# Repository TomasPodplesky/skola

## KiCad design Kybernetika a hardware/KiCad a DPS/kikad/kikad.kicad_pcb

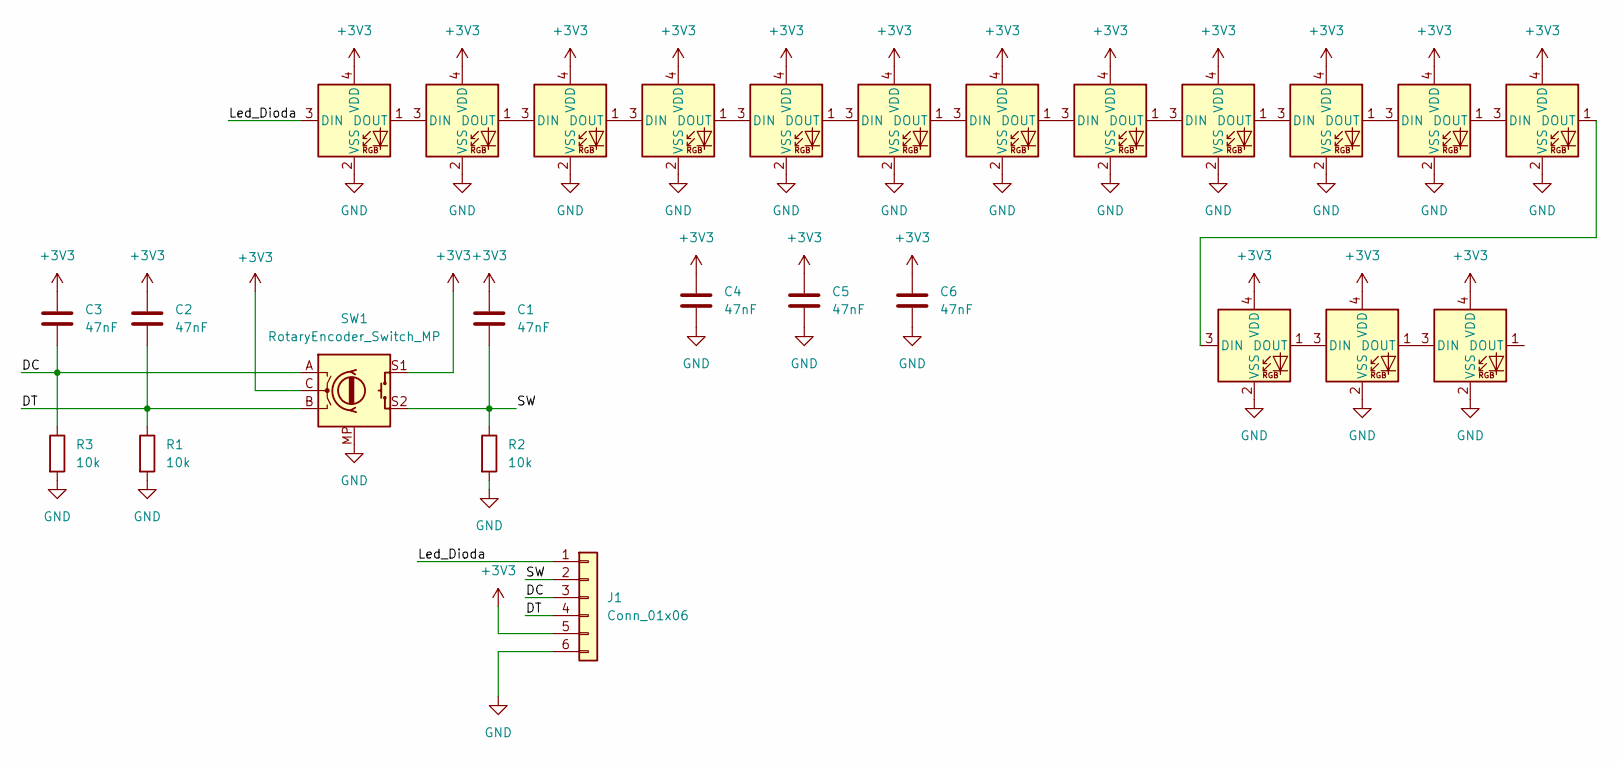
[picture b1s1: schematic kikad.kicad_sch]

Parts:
C1, C2, C3, C4, C5, C6: 47nF; C_0603_1608Metric_Pad1.08x0.95mm_HandSolder
D1, D2, D3, D4, D5, D6, D7, D8, D9, D10, D11, D12, D13, D14, D15: WS2812B-2020; LED_WS2812B-2020_PLCC4_2.0x2.0mm
J1: Conn_01x06; JST_XH_B6B-XH-AM_1x06_P2.50mm_Vertical
R1, R2, R3: 10k; R_0603_1608Metric_Pad0.98x0.95mm_HandSolder
SW1: RotaryEncoder_Switch_MP; RotaryEncoder_Alps_EC11E-Switch_Vertical_H20mm_CircularMoun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

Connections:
+3V3: C1.1, C2.1, C3.1, C4.1, C5.1, C6.1, D1.4 (VDD), D2.4 (VDD), D3.4 (VDD), D4.4 (VDD), D5.4 (VDD), D6.4 (VDD), D7.4 (VDD), D8.4 (VDD), D9.4 (VDD), D10.4 (VDD), D11.4 (VDD), D12.4 (VDD), D13.4 (VDD), D14.4 (VDD), D15.4 (VDD), J1.5, SW1.C, SW1.S1
/DC: C3.2, J1.3, R3.1, SW1.A
/DT: C2.2, J1.4, R1.1, SW1.B
/Led_Dioda: D1.3 (DIN), J1.1
/SW: C1.2, J1.2, R2.1, SW1.S2
GND: C4.2, C5.2, C6.2, D1.2 (VSS), D2.2 (VSS), D3.2 (VSS), D4.2 (VSS), D5.2 (VSS), D6.2 (VSS), D7.2 (VSS), D8.2 (VSS), D9.2 (VSS), D10.2 (VSS), D11.2 (VSS), D12.2 (VSS), D13.2 (VSS), D14.2 (VSS), D15.2 (VSS), J1.6, R1.2, R2.2, R3.2, SW1.MP
unnamed: D1.1 (DOUT), D2.3 (DIN)
unnamed: D2.1 (DOUT), D3.3 (DIN)
unnamed: D3.1 (DOUT), D4.3 (DIN)
unnamed: D4.1 (DOUT), D5.3 (DIN)
unnamed: D5.1 (DOUT), D6.3 (DIN)
unnamed: D6.1 (DOUT), D7.3 (DIN)
unnamed: D7.1 (DOUT), D8.3 (DIN)
unnamed: D8.1 (DOUT), D9.3 (DIN)
unnamed: D9.1 (DOUT), D10.3 (DIN)
unnamed: D10.1 (DOUT), D11.3 (DIN)
unnamed: D11.1 (DOUT), D12.3 (DIN)
unnamed: D12.1 (DOUT), D13.3 (DIN)
unnamed: D13.1 (DOUT), D14.3 (DIN)
unnamed: D14.1 (DOUT), D15.3 (DIN)

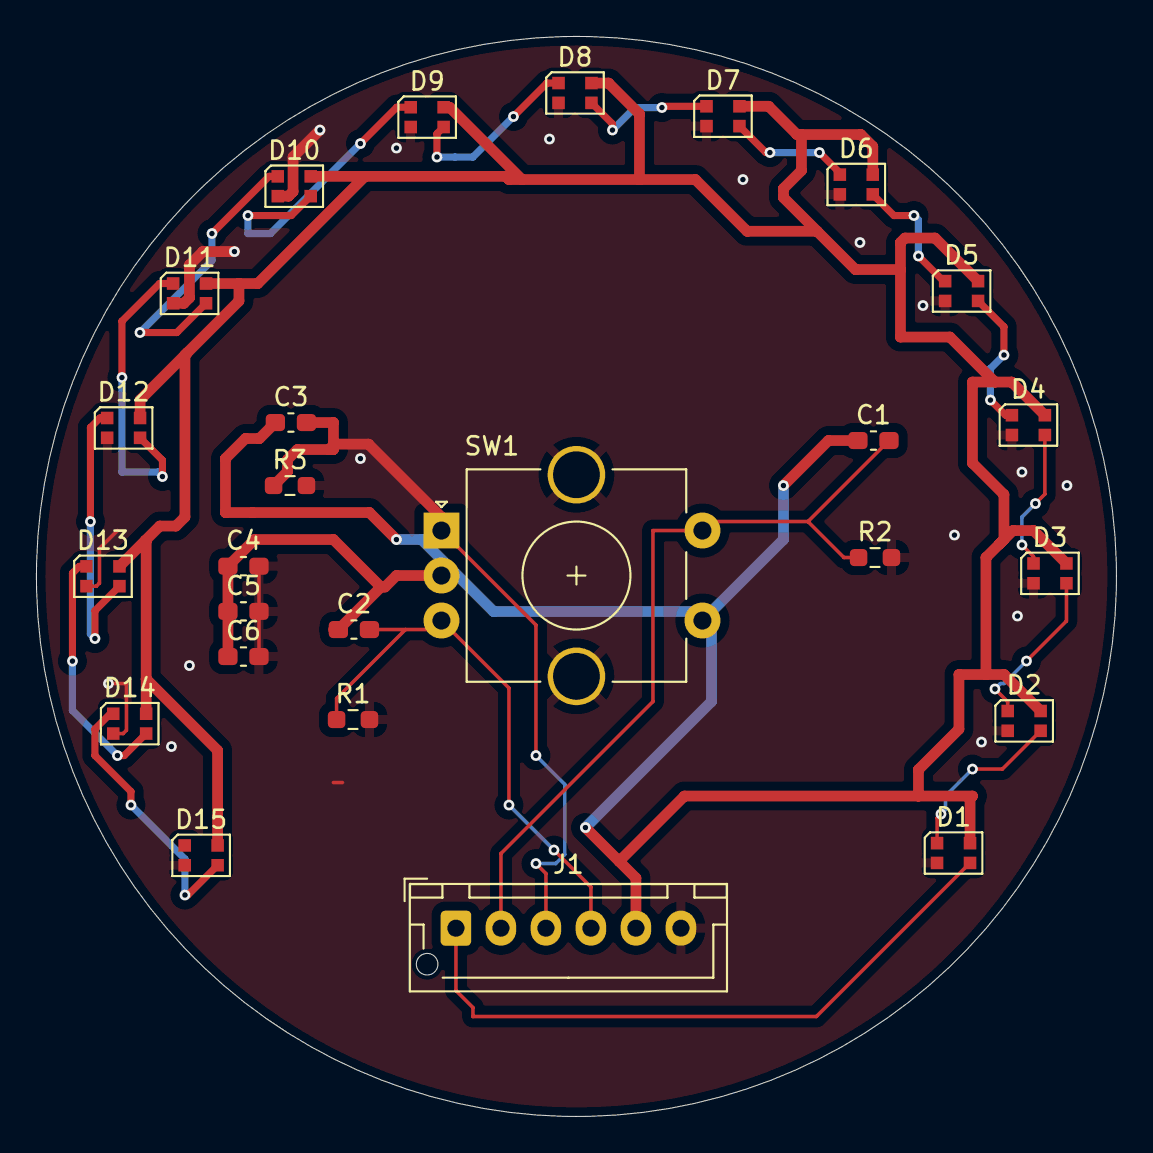
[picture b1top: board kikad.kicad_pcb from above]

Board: 2 copper layers, 60.0 x 60.0 mm, 26 parts (0 on the bottom side), 20 nets.
